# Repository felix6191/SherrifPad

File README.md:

# SherrifPad
Hi , this is my version of the Hackclub Macro PAD , I tried to make it suit my needs as an actual usable product.  I love the Project and I think you can do it too !

here is a look from the bottom 

# SCHEMATICS
Here you can take a look at the schmeatics which shows the differnt connections between the components.

(this is the updated version)

# PCB 
The pcb shows the actual connections and how they are laid out 

# BOM

If you are interested in my Macropad you will need the following parts which you will be all gifted from hackclub if yu register and make your own MacroPad:

- 1x Seeed XIAO RP2040
- 1x 0.91 inch OLED display
- 5x MX-Style switches
- 1x EC11 Rotary encoder
- 5x Blank DSA keycaps (White)
- 2x SK6812 MINI-E LEDs
- 4x M3x16mm screws
- 4x M3x5mx4mm heatset inserts
- 1x 3d-printed knob 
- 1x 3d-printed case

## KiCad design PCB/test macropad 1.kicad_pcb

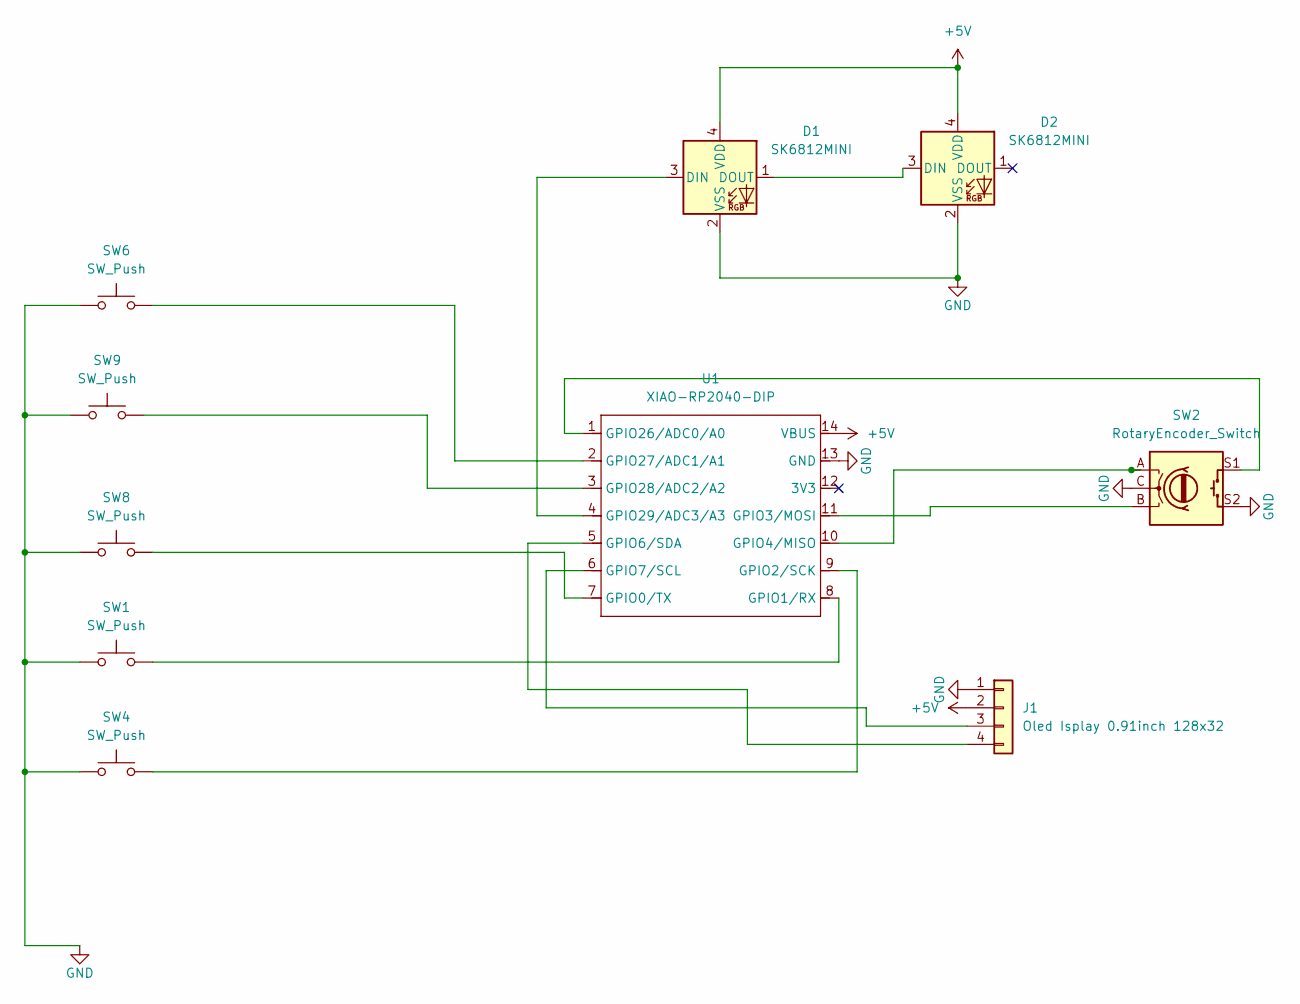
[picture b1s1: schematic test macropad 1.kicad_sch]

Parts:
D1, D2: SK6812MINI; LED_SK6812MINI_PLCC4_3.5x3.5mm_P1.75mm
J1: Oled Isplay 0.91inch 128x32; SSD1306-0.91-OLED-4pin-128x32; Part Number 1-0401FBV0T
SW1, SW4, SW6, SW8, SW9: SW_Push; SW_Cherry_MX_1.00u_PCB
SW2: RotaryEncoder_Switch; RotaryEncoder_Alps_EC11E-Switch_Vertical_H20mm
U1: XIAO-RP2040-DIP; MOUDLE14P-XIAO-DIP-SMD

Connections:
+5V: D1.4 (VDD), D2.4 (VDD), J1.2, U1.14 (VBUS)
GND: D1.2 (VSS), D2.2 (VSS), J1.1, SW1.1, SW2.C, SW2.S2, SW4.1, SW6.1, SW8.1, SW9.1, U1.13 (GND)
unnamed: D1.3 (DIN), U1.4 (GPIO29/ADC3/A3)
unnamed: D1.1 (DOUT), D2.3 (DIN)
unnamed: J1.3, U1.6 (GPIO7/SCL)
unnamed: J1.4, U1.5 (GPIO6/SDA)
unnamed: SW8.2, U1.7 (GPIO0/TX)
unnamed: SW1.2, U1.8 (GPIO1/RX)
unnamed: SW4.2, U1.9 (GPIO2/SCK)
unnamed: SW2.B, U1.11 (GPIO3/MOSI)
unnamed: SW2.A, U1.10 (GPIO4/MISO)
unnamed: SW2.S1, U1.1 (GPIO26/ADC0/A0)
unnamed: SW6.2, U1.2 (GPIO27/ADC1/A1)
unnamed: SW9.2, U1.3 (GPIO28/ADC2/A2)

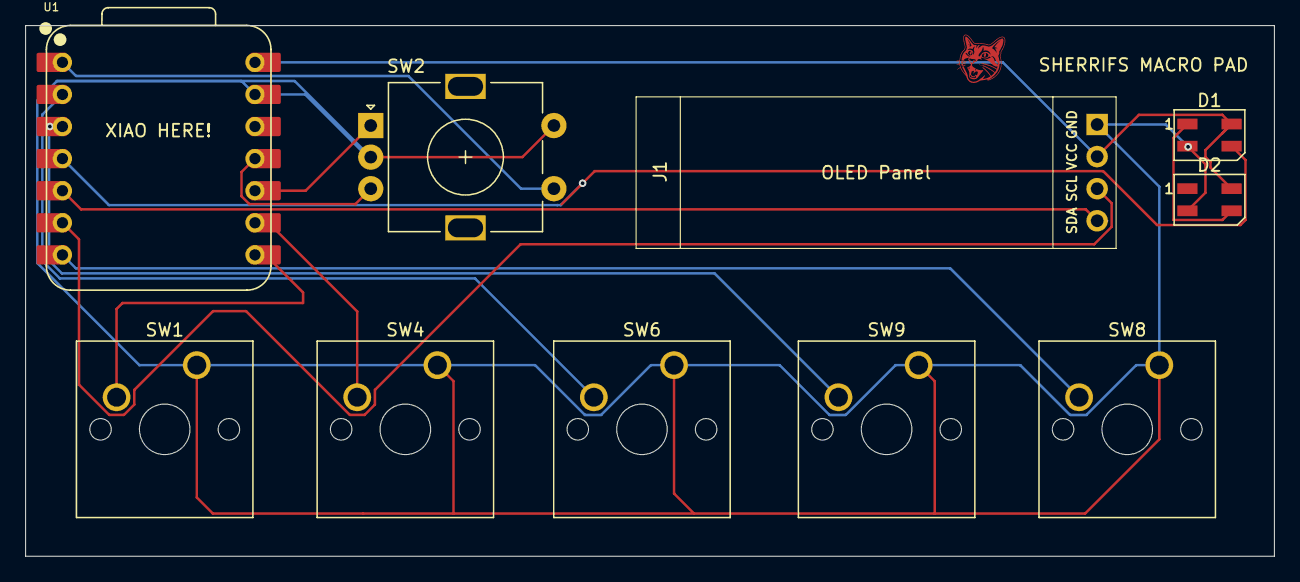
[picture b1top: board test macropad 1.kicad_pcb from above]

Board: 2 copper layers, 98.9 x 42.0 mm, 10 parts (0 on the bottom side), 14 nets.

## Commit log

2026-01-16 Update README with schematics, PCB, and BOM details
    Added sections for schematics, PCB, and BOM with images.
2026-01-16 Fix BOM section header formatting in README.md
2026-01-16 Add README
2026-02-08 finally finished
2026-02-08 Update README with new schematic image
    Added an updated schematic image and a note about it.
2026-02-08 Enhance README with project introduction and images
    Added additional images and introductory text to README.
2026-02-12 final touch and step uploaded
